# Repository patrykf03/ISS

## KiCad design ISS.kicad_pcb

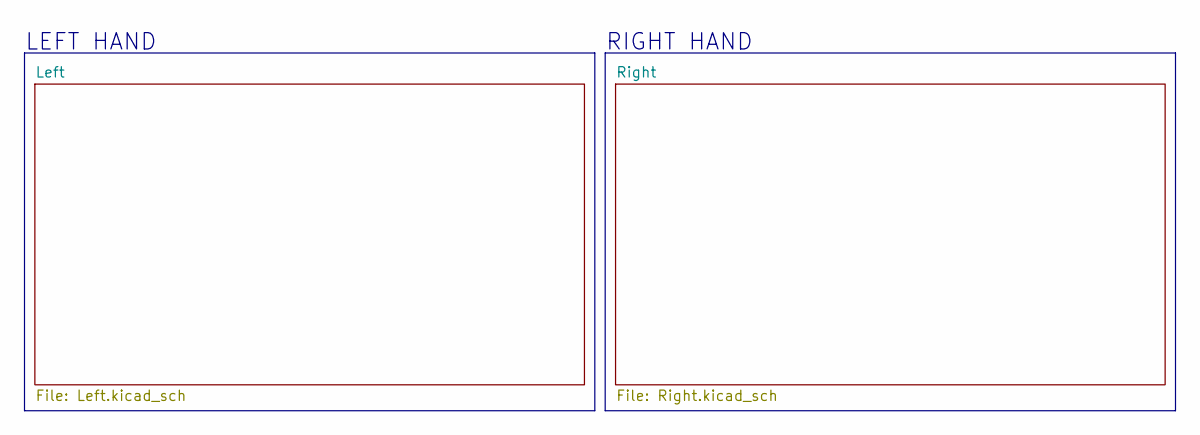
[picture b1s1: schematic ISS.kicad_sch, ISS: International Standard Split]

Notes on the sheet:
RIGHT HAND
LEFT HAND

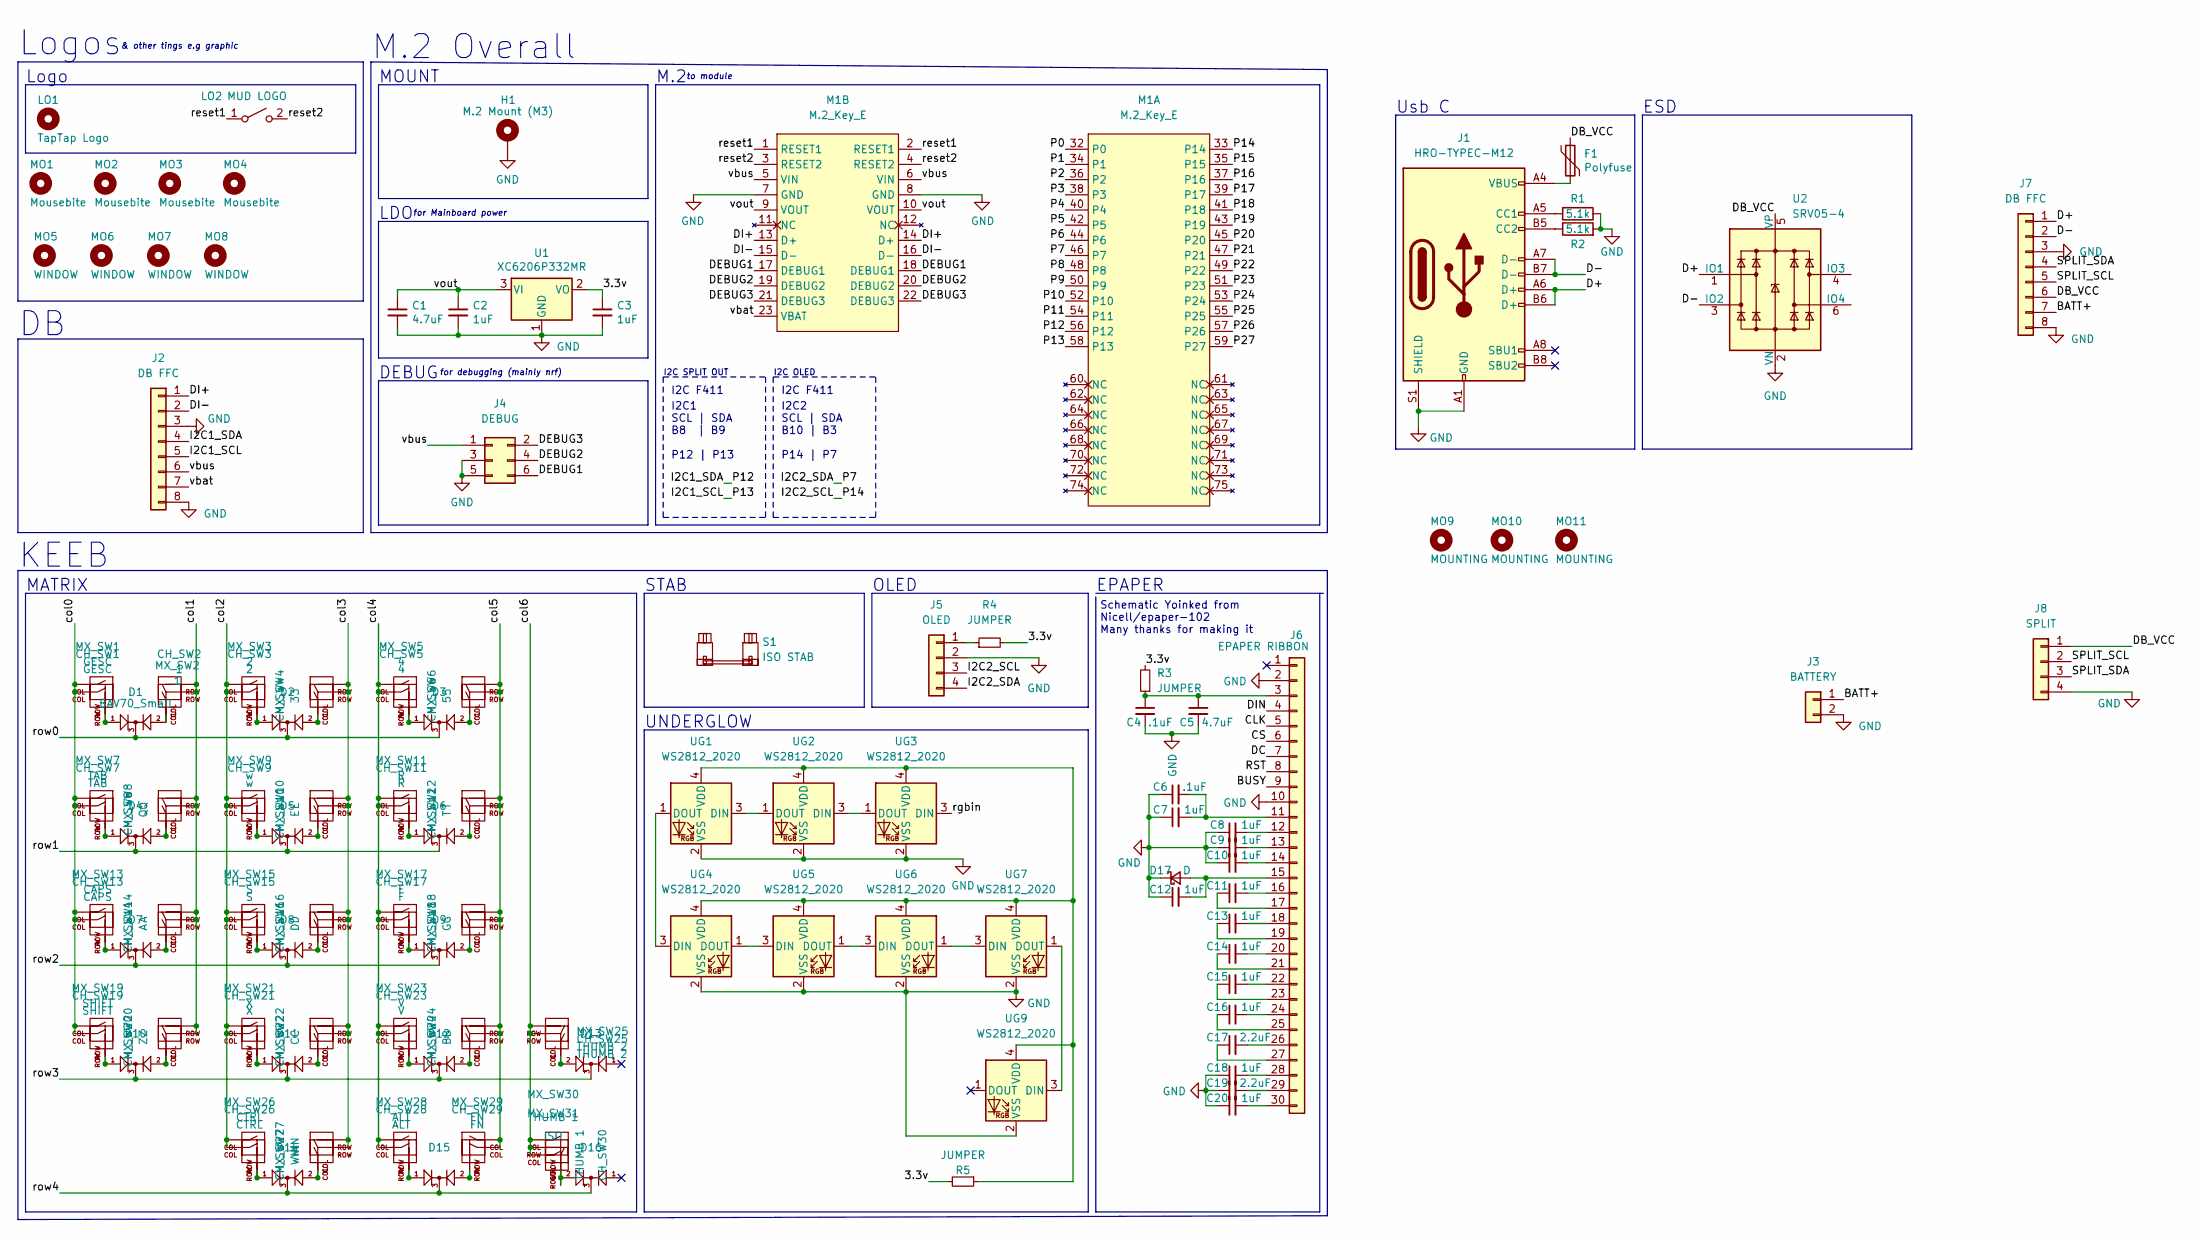
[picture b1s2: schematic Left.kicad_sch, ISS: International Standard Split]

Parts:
C1, C5: 4.7uF; C_0402_1005Metric; LCSC C23733
C2, C3, C7, C8, C9, C10, C11, C12, C13, C14, C15, C16, C18, C20: 1uF; C_0402_1005Metric; LCSC C52923
C4, C6: .1uF; C_0402_1005Metric; LCSC C1525
C17, C19: 2.2uF; C_0402_1005Metric; LCSC C23630
CH_SW1: GESC; SW_choc_HS_1u
CH_SW2: 1; SW_choc_HS_1u
CH_SW3: 2; SW_choc_HS_1u
CH_SW4: 3; SW_choc_HS_1u
CH_SW5: 4; SW_choc_HS_1u
CH_SW6: 5; SW_choc_HS_1u
CH_SW7: TAB; SW_choc_HS_1u
CH_SW8: Q; SW_choc_HS_1u
CH_SW9: w; SW_choc_HS_1u
CH_SW10: E; SW_choc_HS_1u
CH_SW11: R; SW_choc_HS_1u
CH_SW12: T; SW_choc_HS_1u
CH_SW13: CAPS; SW_choc_HS_1u
CH_SW14: A; SW_choc_HS_1u
CH_SW15: S; SW_choc_HS_1u
CH_SW16: D; SW_choc_HS_1u
CH_SW17: F; SW_choc_HS_1u
CH_SW18: G; SW_choc_HS_1u
CH_SW19: SHIFT; SW_choc_HS_1u
CH_SW20: Z; SW_choc_HS_1u
CH_SW21: X; SW_choc_HS_1u
CH_SW22: C; SW_choc_HS_1u
CH_SW23: V; SW_choc_HS_1u
CH_SW24: B; SW_choc_HS_1u
CH_SW25: THUMB 2; SW_choc_HS_1.5u
CH_SW26: CTRL; SW_choc_HS_1u
CH_SW27: WIN; SW_choc_HS_1u
CH_SW28: ALT; SW_choc_HS_1u
CH_SW29: FN; SW_choc_HS_1u
CH_SW30: THUMB 1; SW_choc_HS_1.25u
D1: BAV70_Small; SOT-23
D2, D3, D4, D5, D6, D7, D8, D9, D10, D11, D12, D13, D14, D15, D16: SOT-23
D17: D; D_SOD-123; LCSC C8598
F1: Polyfuse; R_0805_2012Metric
H1: M.2 Mount (M3); MountingHole_3.2mm_M3_DIN965_Pad
J1: HRO-TYPEC-M12; USB_C_Receptacle_HRO_TYPE-C-31-M-12
J2, J7: DB FFC; 100519220810EHLF
J3: BATTERY; JST_PH_S2B-PH-SM4-TB_1x02-1MP_P2.00mm_Horizontal
J4: DEBUG; PinSocket_2x03_P2.54mm_Vertical
J5: OLED; 128x64OLED
J6: EPAPER RIBBON; 100519223010ELF
J8: SPLIT; Magnetic Pogo 4 pin
LO1: TapTap Logo; tt_4mm
LO2: MUD LOGO; LogoSmall_Cu
M1: M.2_Key_E; m2-bracket-key-e
MO1, MO2, MO3, MO4: Mousebite; mousebites_2mm
MO5, MO6, MO7, MO8: WINDOW; MountingHole_2.2mm_M2_Pad
MO9, MO10, MO11: MOUNTING; MountingHole_2.2mm_M2_Pad
MX_SW1: GESC; SW_MX_HS_1u
MX_SW2: 1; SW_MX_HS_1u
MX_SW3: 2; SW_MX_HS_1u
MX_SW4: 3; SW_MX_HS_1u
MX_SW5: 4; SW_MX_HS_1u
MX_SW6: 5; SW_MX_HS_1u
MX_SW7: TAB; SW_MX_HS_1u
MX_SW8: Q; SW_MX_HS_1u
MX_SW9: w; SW_MX_HS_1u
MX_SW10: E; SW_MX_HS_1u
MX_SW11: R; SW_MX_HS_1u
MX_SW12: T; SW_MX_HS_1u
MX_SW13: CAPS; SW_MX_HS_1u
MX_SW14: A; SW_MX_HS_1u
MX_SW15: S; SW_MX_HS_1u
MX_SW16: D; SW_MX_HS_1u
MX_SW17: F; SW_MX_HS_1u
MX_SW18: G; SW_MX_HS_1u
MX_SW19: SHIFT; SW_MX_HS_1u
MX_SW20: Z; SW_MX_HS_1u
MX_SW21: X; SW_MX_HS_1u
MX_SW22: C; SW_MX_HS_1u
MX_SW23: V; SW_MX_HS_1u
MX_SW24: B; SW_MX_HS_1u
MX_SW25: THUMB 2; SW_MX_HS_1.5u
MX_SW26: CTRL; SW_MX_HS_1u
MX_SW27: WIN; SW_MX_HS_1u
MX_SW28: ALT; SW_MX_HS_1u
MX_SW29: FN; SW_MX_HS_1u
MX_SW30: THUMB 1; SW_MX_HS_1.25u
MX_SW31: ISO; SW_MX_HS_1u
R1, R2: 5.1k; R_0402_1005Metric
R3, R4, R5: JUMPER; R_0805_2012Metric
S1: ISO STAB; STAB_MX_ISO_FLIPPED
U1: XC6206P332MR; SOT-23; LCSC C5446
U2: SRV05-4; SOT-23-6
UG1, UG2, UG3, UG4, UG5, UG6, UG7, UG9: WS2812_2020; LED_WS2812_2020

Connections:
/Left/3.3v: C3.1, R3.2, R4.2, R5.2, U1.2 (VO)
/Left/BATT+: J3.1, J7.7
/Left/BUSY: J6.9
/Left/CLK: J6.5
/Left/CS: J6.6
/Left/D+: J1.A6 (D+), J1.B6 (D+), J7.1, U2.1 (IO1)
/Left/D-: J1.A7 (D-), J1.B7 (D-), J7.2, U2.3 (IO2)
/Left/DB_VCC: F1.1, J7.6, J8.1, U2.5 (VP)
/Left/DC: J6.7
/Left/DEBUG1: J4.6, M1.17 (DEBUG1), M1.18 (DEBUG1)
/Left/DEBUG2: J4.4, M1.19 (DEBUG2), M1.20 (DEBUG2)
/Left/DEBUG3: J4.2, M1.21 (DEBUG3), M1.22 (DEBUG3)
/Left/DI+: J2.1, M1.13 (D+), M1.14 (D+)
/Left/DI-: J2.2, M1.15 (D-), M1.16 (D-)
/Left/DIN: J6.4
/Left/I2C1_SCL: J2.5, M1.58 (P13)
/Left/I2C1_SDA: J2.4, M1.56 (P12)
/Left/I2C2_SCL: J5.3, M1.33 (P14)
/Left/I2C2_SDA: J5.4, M1.46 (P7)
/Left/P0: M1.32 (P0)
/Left/P1: M1.34 (P1)
/Left/P2: M1.36 (P2)
/Left/P3: M1.38 (P3)
/Left/P4: M1.40 (P4)
/Left/P5: M1.42 (P5)
/Left/P6: M1.44 (P6)
/Left/P8: M1.48 (P8)
/Left/P9: M1.50 (P9)
/Left/P10: M1.52 (P10)
/Left/P11: M1.54 (P11)
/Left/P15: M1.35 (P15)
/Left/P16: M1.37 (P16)
/Left/P17: M1.39 (P17)
/Left/P18: M1.41 (P18)
/Left/P19: M1.43 (P19)
/Left/P20: M1.45 (P20)
/Left/P21: M1.47 (P21)
/Left/P22: M1.49 (P22)
/Left/P23: M1.51 (P23)
/Left/P24: M1.53 (P24)
/Left/P25: M1.55 (P25)
/Left/P26: M1.57 (P26)
/Left/P27: M1.59 (P27)
/Left/RST: J6.8
/Left/SPLIT_SCL: J7.5, J8.2
/Left/SPLIT_SDA: J7.4, J8.3
/Left/col0: CH_SW1.1 (COL), CH_SW7.1 (COL), CH_SW13.1 (COL), CH_SW19.1 (COL), MX_SW1.1 (COL), MX_SW7.1 (COL), MX_SW13.1 (COL), MX_SW19.1 (COL)
/Left/col1: CH_SW2.2 (ROW), CH_SW8.2 (ROW), CH_SW14.2 (ROW), CH_SW20.2 (ROW), MX_SW2.2 (ROW), MX_SW8.2 (ROW), MX_SW14.2 (ROW), MX_SW20.2 (ROW)
/Left/col2: CH_SW3.1 (COL), CH_SW9.1 (COL), CH_SW15.1 (COL), CH_SW21.1 (COL), CH_SW26.1 (COL), MX_SW3.1 (COL), MX_SW9.1 (COL), MX_SW15.1 (COL), MX_SW21.1 (COL), MX_SW26.1 (COL)
/Left/col3: CH_SW4.2 (ROW), CH_SW10.2 (ROW), CH_SW16.2 (ROW), CH_SW22.2 (ROW), CH_SW27.2 (ROW), MX_SW4.2 (ROW), MX_SW10.2 (ROW), MX_SW16.2 (ROW), MX_SW22.2 (ROW), MX_SW27.2 (ROW)
/Left/col4: CH_SW5.1 (COL), CH_SW11.1 (COL), CH_SW17.1 (COL), CH_SW23.1 (COL), CH_SW28.1 (COL), MX_SW5.1 (COL), MX_SW11.1 (COL), MX_SW17.1 (COL), MX_SW23.1 (COL), MX_SW28.1 (COL)
/Left/col5: CH_SW6.2 (ROW), CH_SW12.2 (ROW), CH_SW18.2 (ROW), CH_SW24.2 (ROW), CH_SW29.1 (COL), MX_SW6.2 (ROW), MX_SW12.2 (ROW), MX_SW18.2 (ROW), MX_SW24.2 (ROW), MX_SW29.1 (COL)
/Left/col6: CH_SW25.2 (ROW), CH_SW30.2 (ROW), MX_SW25.2 (ROW), MX_SW30.1 (COL), MX_SW31.1 (COL)
/Left/reset1: LO2.1 (A), M1.1 (RESET1), M1.2 (RESET1)
/Left/reset2: LO2.2 (B), M1.3 (RESET2), M1.4 (RESET2)
/Left/rgbin: UG3.3 (DIN)
/Left/row0: D1.3 (K), D2.3 (K), D3.3 (K)
/Left/row1: D4.3 (K), D5.3 (K), D6.3 (K)
/Left/row2: D7.3 (K), D8.3 (K), D9.3 (K)
/Left/row3: D10.3 (K), D11.3 (K), D12.3 (K), D13.3 (K)
/Left/row4: D14.3 (K), D15.3 (K), D16.3 (K)
/Left/vbat: J2.7, M1.23 (VBAT)
/Left/vbus: J2.6, J4.1, M1.5 (VIN), M1.6 (VIN)
/Left/vout: C1.1, C2.1, M1.9 (VOUT), M1.10 (VOUT), U1.3 (VI)
GND: C1.2, C2.2, C3.2, C4.2, C5.2, C6.1, C7.1, C8.1, C9.1, C10.1, C12.1, C18.1, C19.1, C20.1, D17.1 (K), H1.1, J1.A1 (GND), J1.A12 (GND), J1.B1 (GND), J1.B12 (GND), J1.S1 (SHIELD), J2.3, J2.8, J3.2, J4.3, J4.5, J5.2, J6.2, J6.10, J7.3, J7.8, J8.4, M1.7 (GND), M1.8 (GND), R1.1, R2.2, U1.1 (GND), U2.2 (VN), UG1.2 (VSS), UG2.2 (VSS), UG3.2 (VSS), UG4.2 (VSS), UG5.2 (VSS), UG6.2 (VSS), UG7.2 (VSS), UG9.2 (VSS)
unnamed: C4.1, C5.1, J6.3, R3.1
unnamed: C6.2, C7.2, J6.11
unnamed: C8.2, J6.12
unnamed: C9.2, J6.13
unnamed: C10.2, J6.14
unnamed: C11.1, J6.17
unnamed: C11.2, J6.16
unnamed: C12.2, D17.2 (A), J6.15
unnamed: C13.1, J6.19
unnamed: C13.2, J6.18
unnamed: C14.1, J6.21
unnamed: C14.2, J6.20
unnamed: C15.1, J6.23
unnamed: C15.2, J6.22
unnamed: C16.1, J6.25
unnamed: C16.2, J6.24
unnamed: C17.1, J6.27
unnamed: C17.2, J6.26
unnamed: C18.2, J6.28
unnamed: C19.2, J6.29
unnamed: C20.2, J6.30
unnamed: CH_SW1.2 (ROW), D1.1 (A1), MX_SW1.2 (ROW)
unnamed: CH_SW2.1 (COL), D1.2 (A2), MX_SW2.1 (COL)
unnamed: CH_SW3.2 (ROW), D2.1 (A1), MX_SW3.2 (ROW)
unnamed: CH_SW4.1 (COL), D2.2 (A2), MX_SW4.1 (COL)
unnamed: CH_SW5.2 (ROW), D3.1 (A1), MX_SW5.2 (ROW)
unnamed: CH_SW6.1 (COL), D3.2 (A2), MX_SW6.1 (COL)
unnamed: CH_SW7.2 (ROW), D4.1 (A1), MX_SW7.2 (ROW)
unnamed: CH_SW8.1 (COL), D4.2 (A2), MX_SW8.1 (COL)
unnamed: CH_SW9.2 (ROW), D5.1 (A1), MX_SW9.2 (ROW)
unnamed: CH_SW10.1 (COL), D5.2 (A2), MX_SW10.1 (COL)
unnamed: CH_SW11.2 (ROW), D6.1 (A1), MX_SW11.2 (ROW)
unnamed: CH_SW12.1 (COL), D6.2 (A2), MX_SW12.1 (COL)
unnamed: CH_SW13.2 (ROW), D7.1 (A1), MX_SW13.2 (ROW)
unnamed: CH_SW14.1 (COL), D7.2 (A2), MX_SW14.1 (COL)
unnamed: CH_SW15.2 (ROW), D8.1 (A1), MX_SW15.2 (ROW)
unnamed: CH_SW16.1 (COL), D8.2 (A2), MX_SW16.1 (COL)
unnamed: CH_SW17.2 (ROW), D9.1 (A1), MX_SW17.2 (ROW)
unnamed: CH_SW18.1 (COL), D9.2 (A2), MX_SW18.1 (COL)
unnamed: CH_SW19.2 (ROW), D10.1 (A1), MX_SW19.2 (ROW)
unnamed: CH_SW20.1 (COL), D10.2 (A2), MX_SW20.1 (COL)
unnamed: CH_SW21.2 (ROW), D11.1 (A1), MX_SW21.2 (ROW)
unnamed: CH_SW22.1 (COL), D11.2 (A2), MX_SW22.1 (COL)
unnamed: CH_SW23.2 (ROW), D12.1 (A1), MX_SW23.2 (ROW)
unnamed: CH_SW24.1 (COL), D12.2 (A2), MX_SW24.1 (COL)
unnamed: CH_SW25.1 (COL), D13.2 (A2), MX_SW25.1 (COL)
unnamed: CH_SW26.2 (ROW), D14.1 (A1), MX_SW26.2 (ROW)
unnamed: CH_SW27.1 (COL), D14.2 (A2), MX_SW27.1 (COL)
unnamed: CH_SW28.2 (ROW), D15.1 (A1), MX_SW28.2 (ROW)
unnamed: CH_SW29.2 (ROW), D15.2 (A2), MX_SW29.2 (ROW)
unnamed: CH_SW30.1 (COL), D16.2 (A2), MX_SW30.2 (ROW), MX_SW31.2 (ROW)
unnamed: F1.2, J1.A4 (VBUS), J1.A9 (VBUS), J1.B4 (VBUS), J1.B9 (VBUS)
unnamed: J1.A5 (CC1), R1.2
unnamed: J1.B5 (CC2), R2.1
unnamed: J5.1, R4.1
unnamed: R5.1, UG1.4 (VDD), UG2.4 (VDD), UG3.4 (VDD), UG4.4 (VDD), UG5.4 (VDD), UG6.4 (VDD), UG7.4 (VDD), UG9.4 (VDD)
unnamed: UG1.1 (DOUT), UG4.3 (DIN)
unnamed: UG1.3 (DIN), UG2.1 (DOUT)
unnamed: UG2.3 (DIN), UG3.1 (DOUT)
unnamed: UG4.1 (DOUT), UG5.3 (DIN)
unnamed: UG5.1 (DOUT), UG6.3 (DIN)
unnamed: UG6.1 (DOUT), UG7.3 (DIN)
unnamed: UG7.1 (DOUT), UG9.3 (DIN)

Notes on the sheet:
Logos
I2C F411
KEEB
M.2 Overall
for Mainboard power
& other tings e.g graphic
ESD
I2C2 SCL | SDA B10 | B3 P14 | P7
Usb C
MATRIX
for debugging (mainly nrf)
OLED
I2C OLED
M.2
I2C SPLIT OUT
I2C1 SCL | SDA B8 | B9 P12 | P13
DEBUG
STAB
MOUNT
LDO
to module
Logo
Schematic Yoinked from Nicell/epaper-102 Many thanks for making it
UNDERGLOW
EPAPER

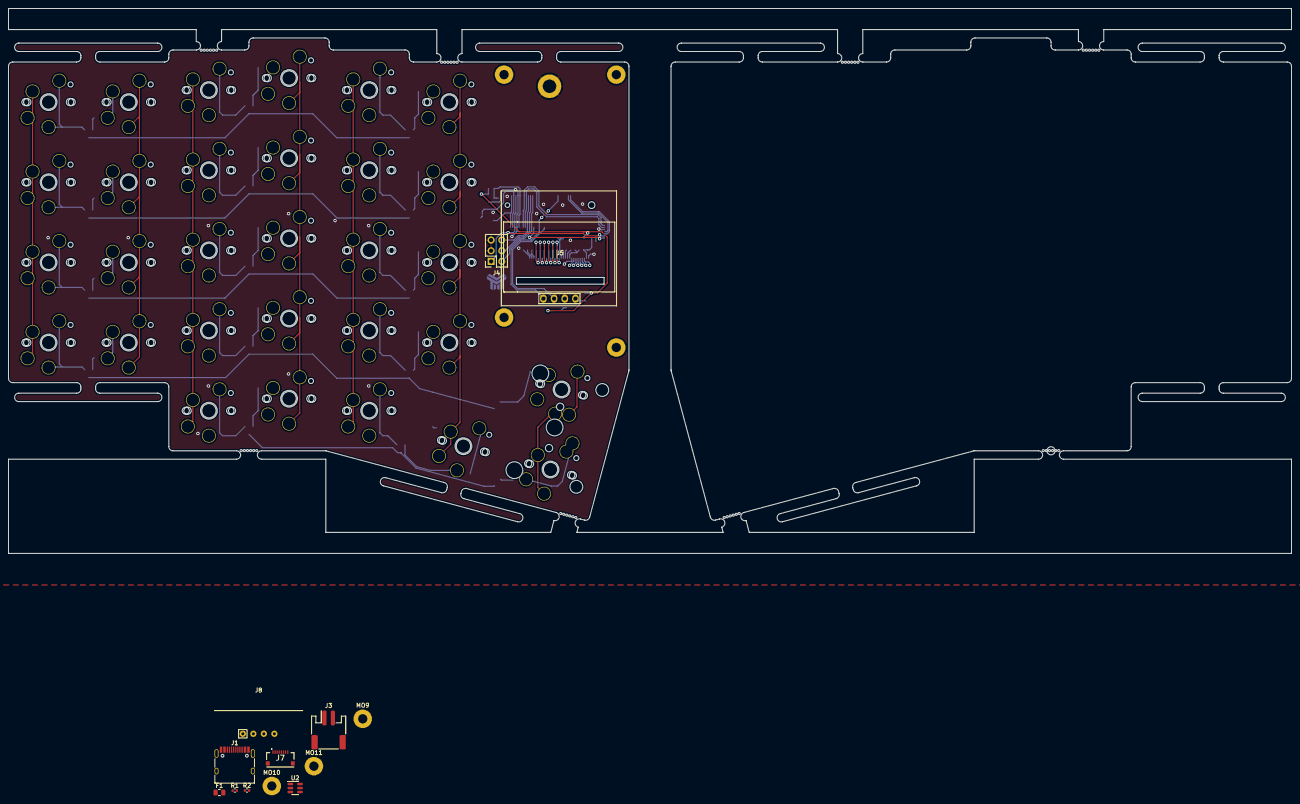
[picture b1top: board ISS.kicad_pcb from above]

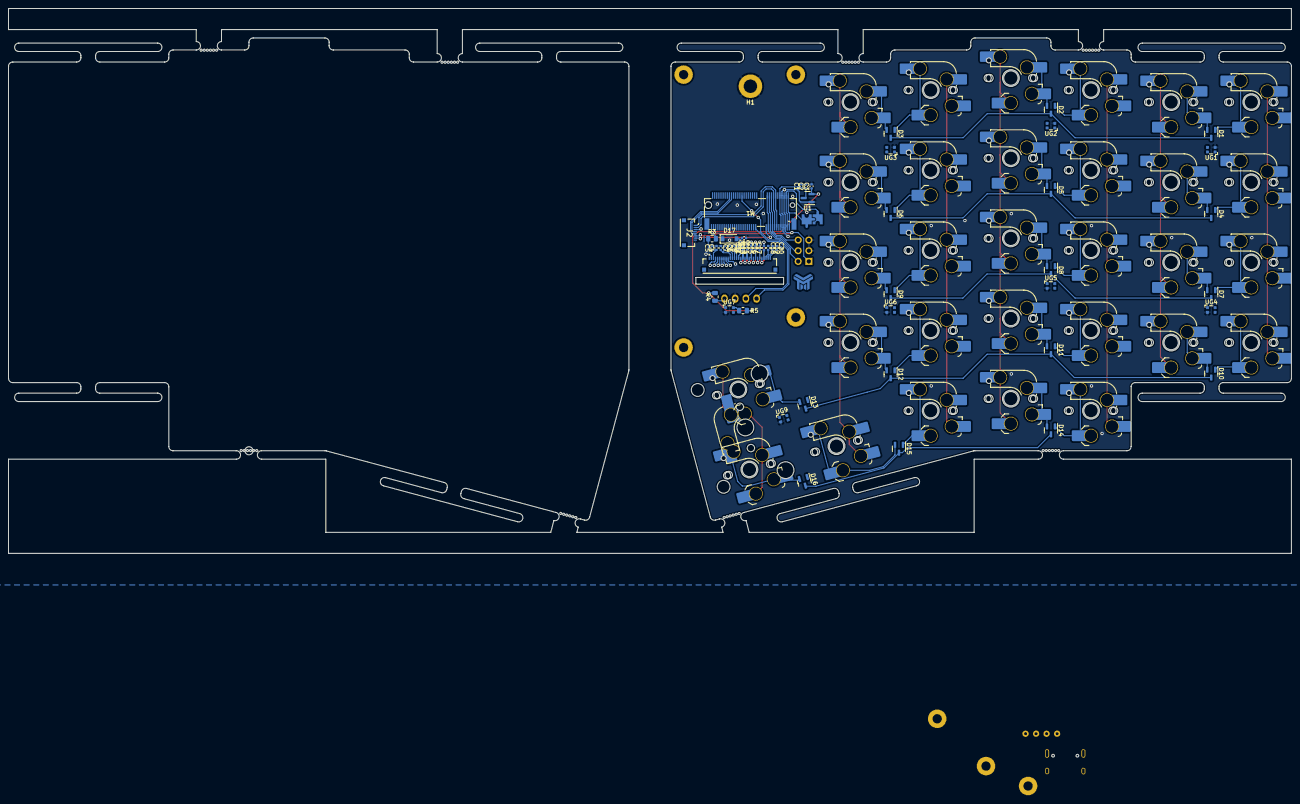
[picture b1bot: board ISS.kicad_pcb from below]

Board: 2 copper layers, 304.9 x 129.5 mm, 142 parts (120 on the bottom side), 97 nets.

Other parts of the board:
MO1#2, MO2#2, MO3#2, MO4#2: Mousebite; mousebites_2mm

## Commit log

2022-03-28 add gitignore
2022-03-28 fix gitignore
2022-03-28 start working on the pcb. left half almost done
2022-03-29 start working on adding the db
2022-03-30 db stuff and spi pin deciding spreadsheet
2022-04-01 finish left side. do a bunch of right side. do right db. change db flat ribbon on both
2022-04-02 finish right. fix some things on left. add teardrops
2023-05-11 add nicer logos and shit
